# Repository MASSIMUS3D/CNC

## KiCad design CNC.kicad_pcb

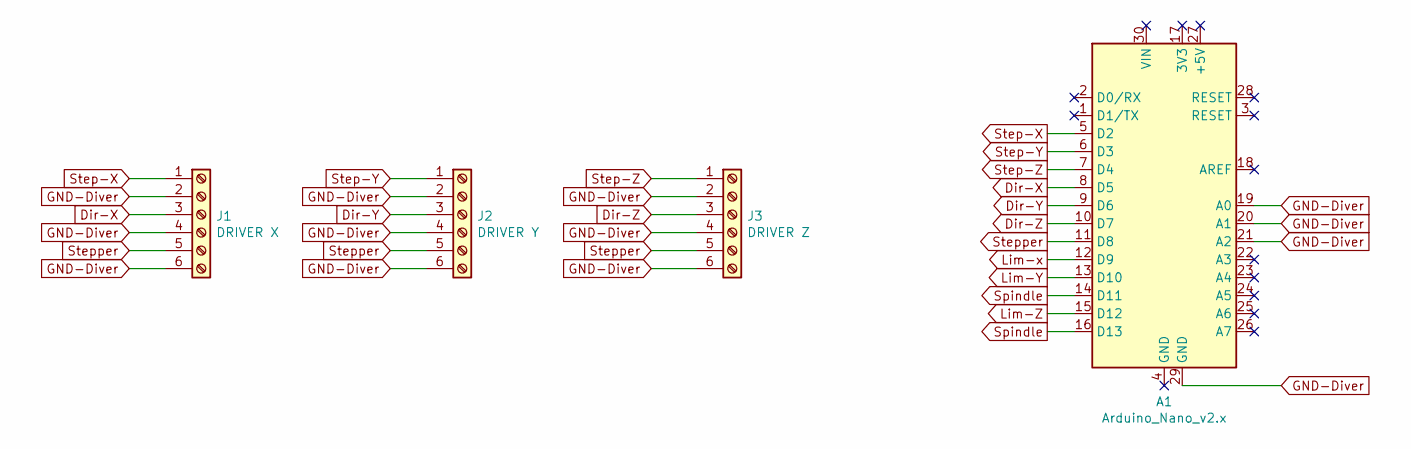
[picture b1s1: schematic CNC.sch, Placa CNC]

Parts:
A1: Arduino_Nano_v2.x; Arduino_Nano
J1: DRIVER X; Altech_AK300_1x06_P5.00mm_45-Degree
J2: DRIVER Y; Altech_AK300_1x06_P5.00mm_45-Degree
J3: DRIVER Z; Altech_AK300_1x06_P5.00mm_45-Degree

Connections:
Dir-X: A1.8 (D5), J1.3
Dir-Y: A1.9 (D6), J2.3
Dir-Z: A1.10 (D7), J3.3
GND-Diver: A1.19 (A0), A1.20 (A1), A1.21 (A2), A1.29 (GND), J1.2, J1.4, J1.6, J2.2, J2.4, J2.6, J3.2, J3.4, J3.6
Lim-Y: A1.13 (D10)
Lim-Z: A1.15 (D12)
Lim-x: A1.12 (D9)
Spindle: A1.14 (D11), A1.16 (D13)
Step-X: A1.5 (D2), J1.1
Step-Y: A1.6 (D3), J2.1
Step-Z: A1.7 (D4), J3.1
Stepper: A1.11 (D8), J1.5, J2.5, J3.5

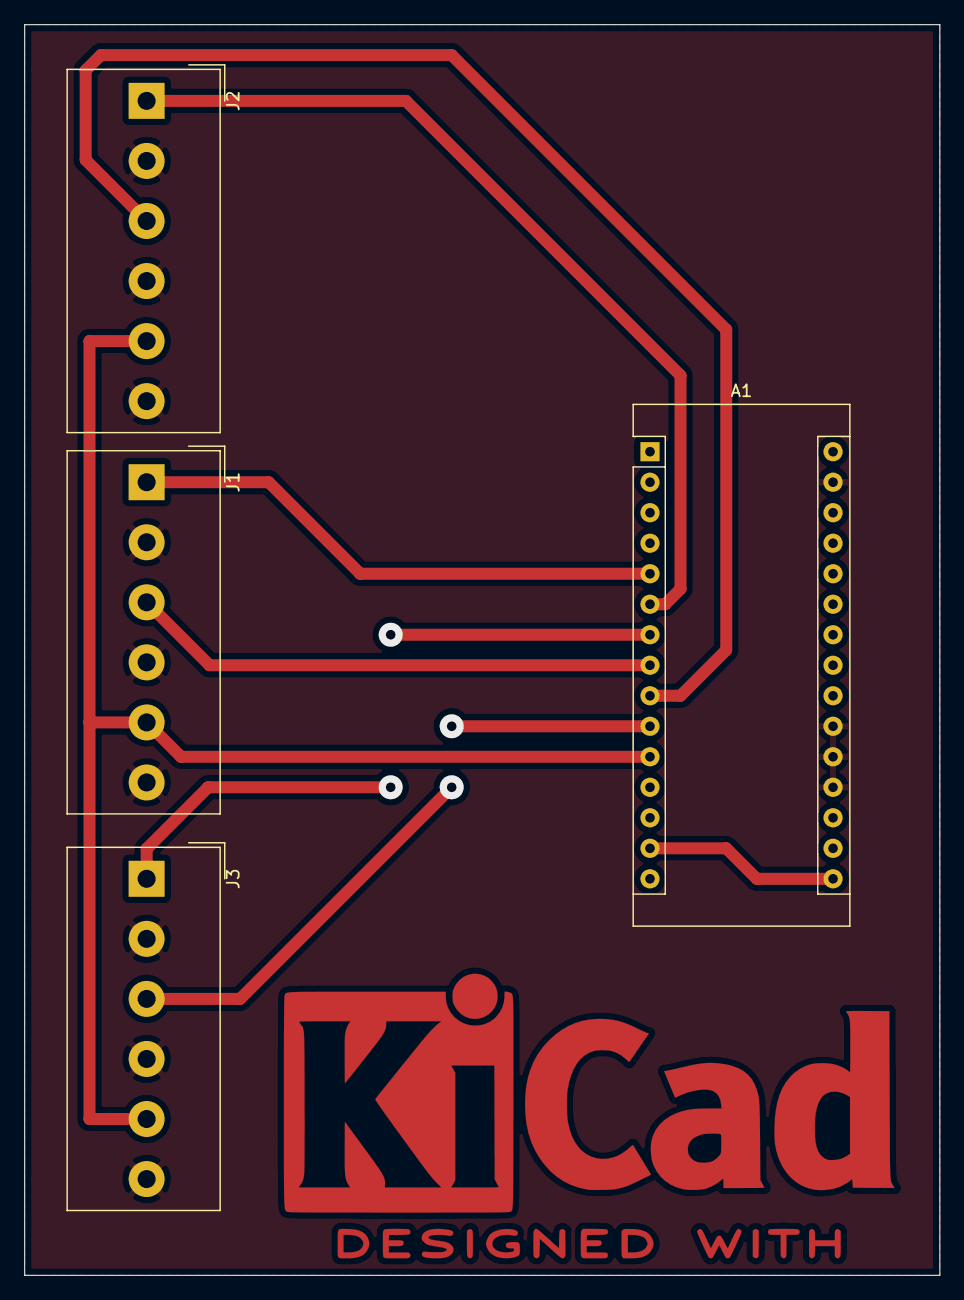
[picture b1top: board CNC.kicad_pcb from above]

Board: 2 copper layers, 76.2 x 104.1 mm, 4 parts (0 on the bottom side), 9 nets.

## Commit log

2019-11-08 Principal
2019-11-08 Render
2019-11-11 Atualização
